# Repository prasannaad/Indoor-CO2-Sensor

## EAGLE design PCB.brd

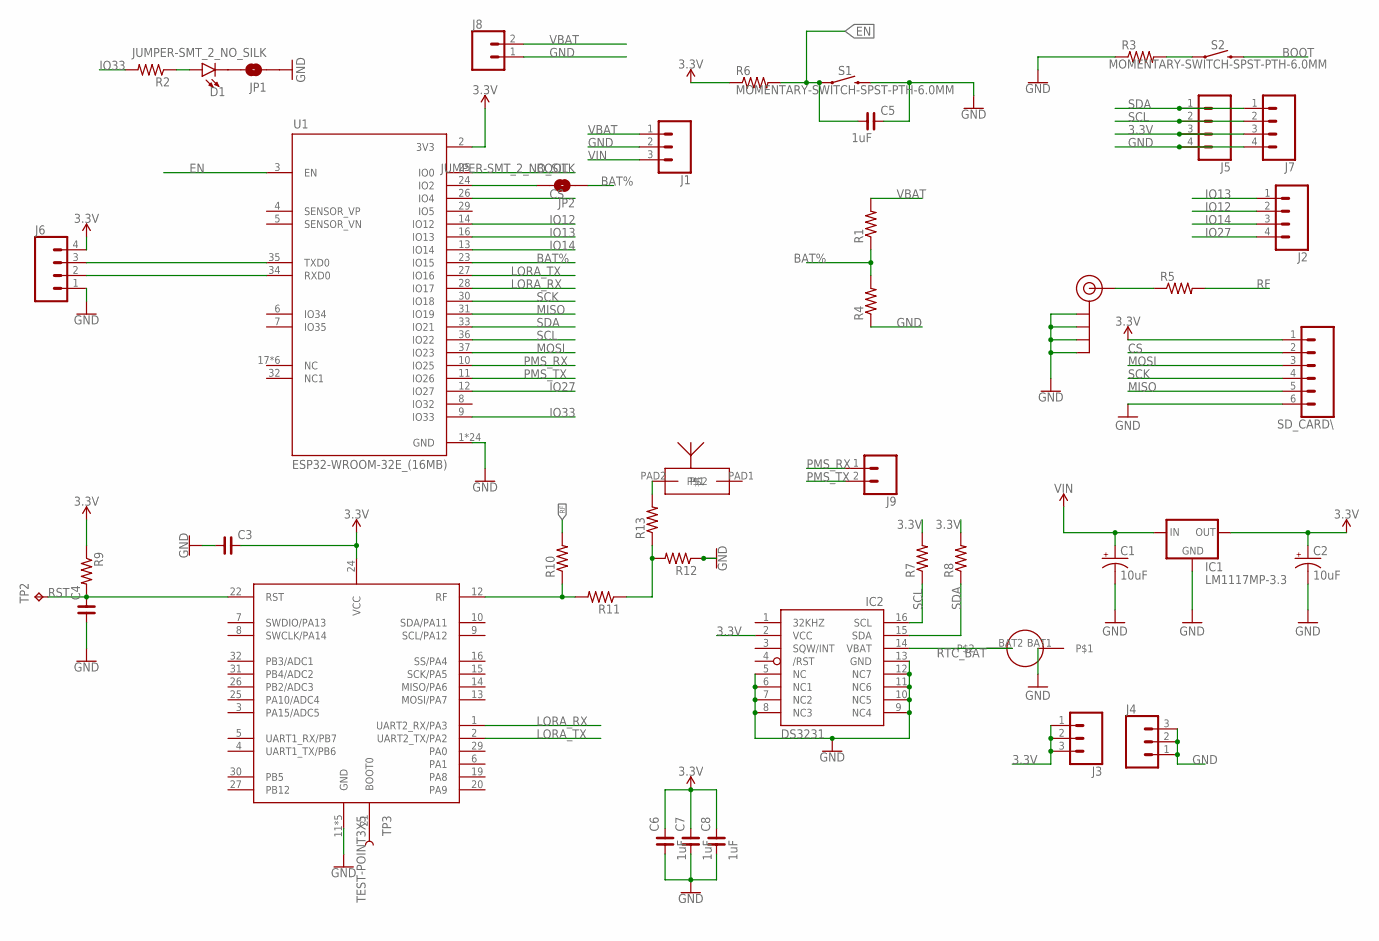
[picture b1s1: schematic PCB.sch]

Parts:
C1, C2: 10uF; EIA3216
C3, C4: C_0805; C0805
C5, C6, C7, C8: 1uF; C0805
D1: LED1206; LED-1206
IC1: LM1117MP-3.3; SOT223
IC2: DS3231/SO; SO16W
J1, J3, J4: CONN_031X03_NO_SILK; 1X03_NO_SILK
J2, J5, J6, J7: CONN_041X04_NO_SILK; 1X04_NO_SILK
J8, J9: CONN_021X02_NO_SILK; 1X02_NO_SILK
J$1: SMA_EDGE; SMA-EDGE
JP1, JP2: JUMPER-SMT_2_NO_SILK; SMT-JUMPER_2_NO_SILK
R1, R2, R3, R4, R5, R6, R7, R8, R9, R10, R11, R12, R13: CRCW08050000Z0EA; RES_0805
S1, S2: MOMENTARY-SWITCH-SPST-PTH-6.0MM; TACTILE_SWITCH_PTH_6.0MM
SD_CARD\: CONN_06NO_SILK_FEMALE_PTH; 1X06_NO_SILK
TP2: TPTP12R; TP12R
TP3: TEST-POINT3X5; PAD.03X.05
U1: ESP32-WROOM-32E_(16MB); MODULE_ESP32-WROOM-32E_(16MB)
U$1: RAK3172HF; RAK3172
U$2: CR1220_HOLDER
U$9: NN02-224

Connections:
3.3V: C2.A (+), C3.2, C6.2, C7.2, C8.2, IC1.2 (OUT), IC1.4 (OUT), IC2.2 (VCC), J3.1, J3.2, J3.3, J5.3, J6.4, J7.3, R6.1, R7.2, R8.2, R9.1, SD_CARD\.1, U1.2 (3V3), U$1.24 (VCC)
BAT%: JP2.1, R1.1, R4.2, U1.23 (IO15)
BOOT: S2.3 (2), U1.25 (IO0)
CS: SD_CARD\.2, U1.26 (IO4)
EN: C5.1, R6.2, S1.1, U1.3 (EN)
GND: C1.C (-), C2.C (-), C3.1, C4.1, C5.2, C6.1, C7.1, C8.1, IC1.1 (GND), IC2.5 (NC), IC2.6 (NC1), IC2.7 (NC2), IC2.8 (NC3), IC2.9 (NC4), IC2.10 (NC5), IC2.11 (NC6), IC2.12 (NC7), IC2.13 (GND), J1.2, J4.1, J4.2, J4.3, J5.4, J6.1, J7.4, J8.1, J$1.GND@0 (GND), J$1.GND@1 (GND), J$1.GND@2 (GND), J$1.GND@3 (GND), JP1.1, R3.1, R4.1, R12.1, S1.3 (2), SD_CARD\.6, U1.1 (GND), U1.15 (GND), U1.38 (GND), U1.39_1 (GND), U1.39_2 (GND), U1.39_3 (GND), U1.39_4 (GND), U1.39_5 (GND), U1.39_6 (GND), U1.39_7 (GND), U1.39_8 (GND), U1.39_9 (GND), U1.39_10 (GND), U1.39_11 (GND), U1.39_12 (GND), U1.39_13 (GND), U1.39_14 (GND), U1.39_15 (GND), U1.39_16 (GND), U1.39_17 (GND), U1.39_18 (GND), U1.39_19 (GND), U1.39_20 (GND), U1.39_21 (GND), U$1.11 (GND), U$1.17 (GND), U$1.18 (GND), U$1.23 (GND), U$1.28 (GND), U$2.BAT1
IO12: J2.2, U1.14 (IO12)
IO13: J2.1, U1.16 (IO13)
IO14: J2.3, U1.13 (IO14)
IO27: J2.4, U1.12 (IO27)
IO33: R2.2, U1.9 (IO33)
LORA_RX: U1.28 (IO17), U$1.1 (UART2_RX/PA3)
LORA_TX: U1.27 (IO16), U$1.2 (UART2_TX/PA2)
MISO: SD_CARD\.5, U1.31 (IO19)
MOSI: SD_CARD\.3, U1.37 (IO23)
unnamed: TP3.P$1, U$1.21 (BOOT0)
unnamed: D1.C, JP1.2
unnamed: R3.2, S2.1
unnamed: J6.3, U1.35 (TXD0)
unnamed: J6.2, U1.34 (RXD0)
unnamed: D1.A, R2.1
unnamed: R13.2, U$9.PAD2
unnamed: J$1.SIG (SIGNAL), R5.1
unnamed: JP2.2, U1.24 (IO2)
unnamed: R11.1, R12.2, R13.1
unnamed: R10.1, R11.2, U$1.12 (RF)
PMS_RX: J9.1, U1.10 (IO25)
PMS_TX: J9.2, U1.11 (IO26)
RF: R5.2, R10.2
RST: C4.2, R9.2, TP2.TP, U$1.22 (RST)
RTC_BAT: IC2.14 (VBAT), U$2.BAT2
SCK: SD_CARD\.4, U1.30 (IO18)
SCL: IC2.16 (SCL), J5.2, J7.2, R7.1, U1.36 (IO22)
SDA: IC2.15 (SDA), J5.1, J7.1, R8.1, U1.33 (IO21)
VBAT: J1.1, J8.2, R1.2
VIN: C1.A (+), IC1.3 (IN), J1.3

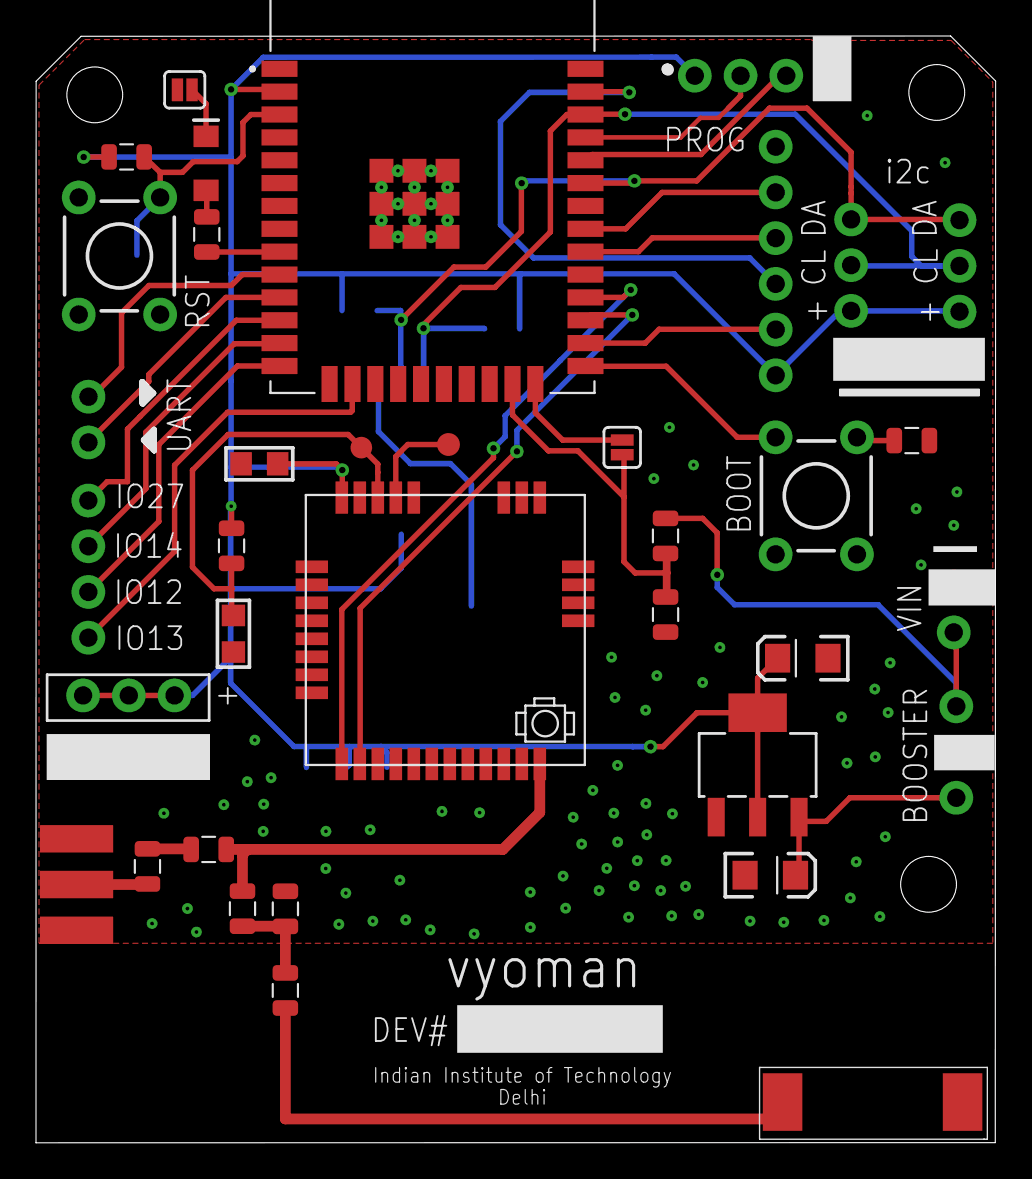
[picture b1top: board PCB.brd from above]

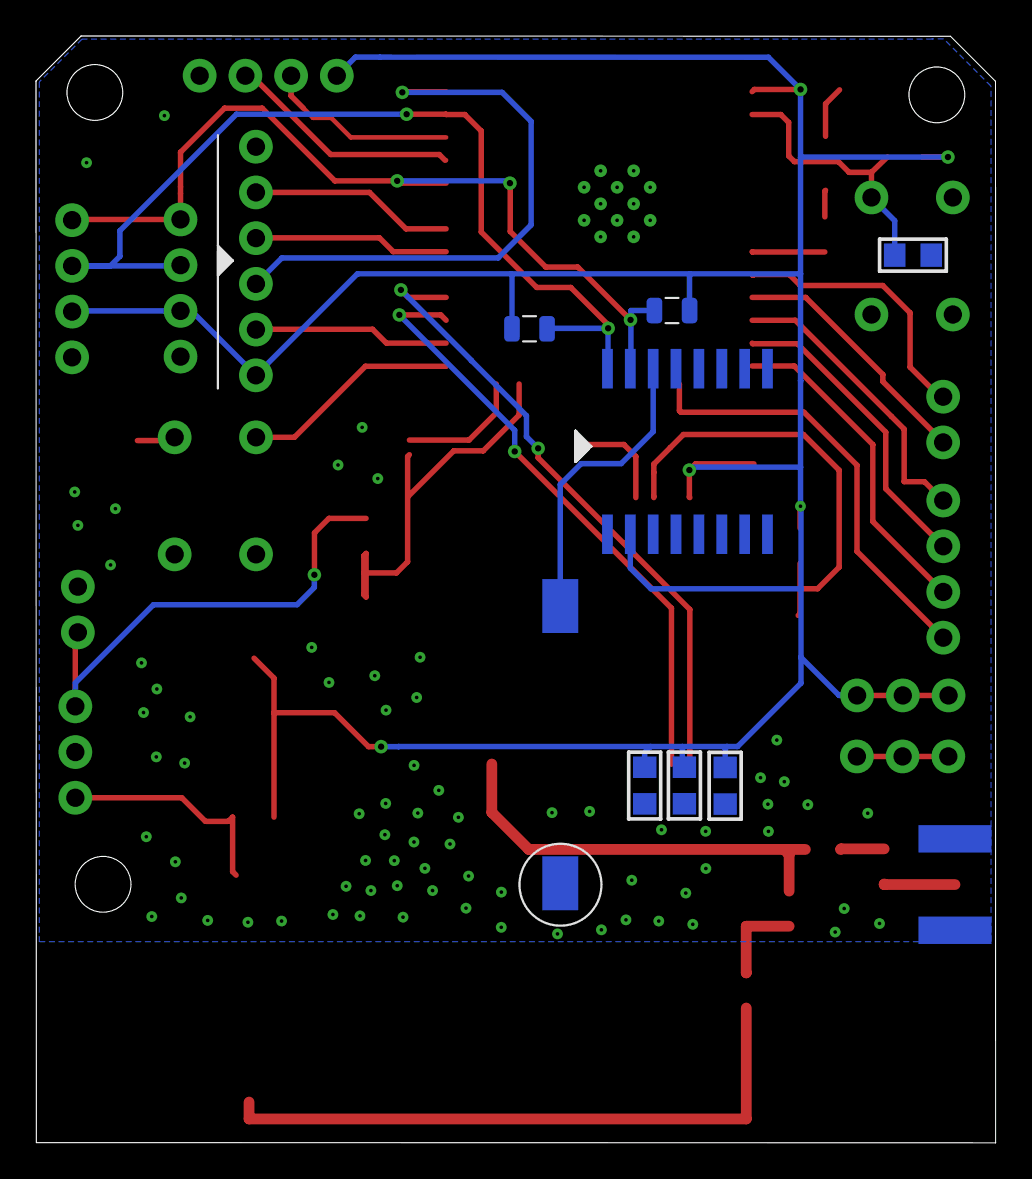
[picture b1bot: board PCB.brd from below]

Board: 2 copper layers, 53.3 x 61.5 mm, 45 parts (8 on the bottom side), 36 nets.

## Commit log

2022-03-07 Create LICENSE

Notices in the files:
parts and their libraries:
SparkFun-Connectors: Licensing: Creative Commons ShareAlike 4.0 International - https://creativecommons.org/licenses/by-sa/4.0
rc-master-smd: Copyright (C) 2007, Bob Starr
